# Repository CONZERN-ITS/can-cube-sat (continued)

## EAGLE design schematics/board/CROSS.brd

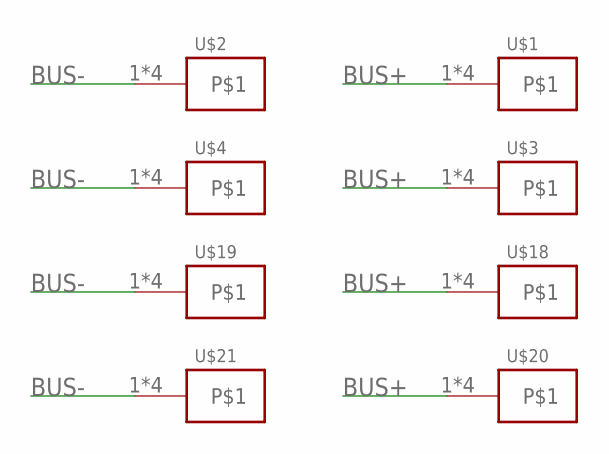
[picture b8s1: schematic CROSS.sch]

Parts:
U$1, U$2, U$3, U$4, U$18, U$19, U$20, U$21: KCONNECT-

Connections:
BUS+: U$1.1, U$1.2, U$1.3, U$1.4, U$3.1, U$3.2, U$3.3, U$3.4, U$18.1, U$18.2, U$18.3, U$18.4, U$20.1, U$20.2, U$20.3, U$20.4
BUS-: U$2.1, U$2.2, U$2.3, U$2.4, U$4.1, U$4.2, U$4.3, U$4.4, U$19.1, U$19.2, U$19.3, U$19.4, U$21.1, U$21.2, U$21.3, U$21.4

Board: 2 copper layers, 8 parts (0 on the bottom side), 2 nets, no tracks yet.

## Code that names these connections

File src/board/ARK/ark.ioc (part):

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Mcu.Name=STM32F103C(8-B)Tx
Mcu.Package=LQFP48
Mcu.UserName=STM32F103C8Tx
PA1.GPIOParameters=GPIO_Speed,PinState,GPIO_PuPd,GPIO_Label,GPIO_ModeDefaultOutputPP
PA1.GPIO_Label=BMS5
PA1.GPIO_ModeDefaultOutputPP=GPIO_MODE_OUTPUT_OD
PA1.GPIO_PuPd=GPIO_NOPULL
PA1.GPIO_Speed=GPIO_SPEED_FREQ_LOW
PA1.PinState=GPIO_PIN_SET
PA1.Signal=GPIO_Output
PA10.Mode=Asynchronous
PA10.Signal=USART1_RX
PA13.Mode=Serial_Wire
PA13.Signal=SYS_JTMS-SWDIO
PA14.Mode=Serial_Wire
PA14.Signal=SYS_JTCK-SWCLK
PA2.GPIOParameters=GPIO_Speed,PinState,GPIO_PuPd,GPIO_Label,GPIO_ModeDefaultOutputPP
PA2.GPIO_Label=BMS6
PA2.GPIO_ModeDefaultOutputPP=GPIO_MODE_OUTPUT_OD
PA2.GPIO_PuPd=GPIO_NOPULL
PA2.GPIO_Speed=GPIO_SPEED_FREQ_LOW
PA2.PinState=GPIO_PIN_SET
PA2.Signal=GPIO_Output
PA3.GPIOParameters=GPIO_Speed,PinState,GPIO_PuPd,GPIO_Label,GPIO_ModeDefaultOutputPP
PA3.GPIO_Label=BMS3
PA3.GPIO_ModeDefaultOutputPP=GPIO_MODE_OUTPUT_OD
PA3.GPIO_PuPd=GPIO_NOPULL
PA3.GPIO_Speed=GPIO_SPEED_FREQ_LOW
PA3.PinState=GPIO_PIN_SET
PA3.Signal=GPIO_Output
PA4.GPIOParameters=GPIO_Speed,PinState,GPIO_PuPd,GPIO_Label,GPIO_ModeDefaultOutputPP
PA4.GPIO_Label=BMS4
PA4.GPIO_ModeDefaultOutputPP=GPIO_MODE_OUTPUT_OD
PA4.GPIO_PuPd=GPIO_NOPULL
PA4.GPIO_Speed=GPIO_SPEED_FREQ_LOW
PA4.PinState=GPIO_PIN_SET
PA4.Signal=GPIO_Output
PA5.GPIOParameters=GPIO_Speed,PinState,GPIO_PuPd,GPIO_Label,GPIO_ModeDefaultOutputPP
PA5.GPIO_Label=BMS1
PA5.GPIO_ModeDefaultOutputPP=GPIO_MODE_OUTPUT_OD
PA5.GPIO_PuPd=GPIO_NOPULL
PA5.GPIO_Speed=GPIO_SPEED_FREQ_LOW
PA5.PinState=GPIO_PIN_SET
PA5.Signal=GPIO_Output
PA6.GPIOParameters=GPIO_Speed,PinState,GPIO_PuPd,GPIO_Label,GPIO_ModeDefaultOutputPP
PA6.GPIO_Label=BMS2
PA6.GPIO_ModeDefaultOutputPP=GPIO_MODE_OUTPUT_OD
PA6.GPIO_PuPd=GPIO_NOPULL
PA6.GPIO_Speed=GPIO_SPEED_FREQ_LOW
PA6.PinState=GPIO_PIN_SET
PA6.Signal=GPIO_Output
PA7.GPIOParameters=GPIO_Speed,PinState,GPIO_PuPd,GPIO_Label,GPIO_ModeDefaultOutputPP
PA7.GPIO_Label=OW
PA7.GPIO_ModeDefaultOutputPP=GPIO_MODE_OUTPUT_OD
PA7.GPIO_PuPd=GPIO_PULLUP
PA7.GPIO_Speed=GPIO_SPEED_FREQ_HIGH
PA7.PinState=GPIO_PIN_SET
PA7.Signal=GPIO_Output
PA9.Mode=Asynchronous
PA9.Signal=USART1_TX
PB0.GPIOParameters=GPIO_PuPd,GPIO_Label
PB0.GPIO_Label=PGOOD1
PB0.GPIO_PuPd=GPIO_PULLUP
PB0.Signal=GPIO_Input
PB1.GPIOParameters=GPIO_PuPd,GPIO_Label
PB1.GPIO_Label=PGOOD2
PB1.GPIO_PuPd=GPIO_PULLUP
PB1.Signal=GPIO_Input
PB10.Mode=I2C
PB10.Signal=I2C2_SCL
PB11.Mode=I2C
PB11.Signal=I2C2_SDA
PB14.GPIOParameters=PinState,GPIO_PuPd,GPIO_Label,GPIO_ModeDefaultOutputPP
PB14.GPIO_Label=DPC_RST
PB14.GPIO_ModeDefaultOutputPP=GPIO_MODE_OUTPUT_OD
PB14.GPIO_PuPd=GPIO_PULLUP
PB14.PinState=GPIO_PIN_SET
PB14.Signal=GPIO_Output
PB15.GPIOParameters=PinState,GPIO_PuPd,GPIO_Label,GPIO_ModeDefaultOutputPP
PB15.GPIO_Label=DPD_RST
PB15.GPIO_ModeDefaultOutputPP=GPIO_MODE_OUTPUT_PP
PB15.GPIO_PuPd=GPIO_PULLUP
PB15.PinState=GPIO_PIN_SET
PB15.Signal=GPIO_Output
PB5.GPIOParameters=GPIO_Speed,PinState,GPIO_PuPd,GPIO_Label,GPIO_ModeDefaultOutputPP
PB5.GPIO_Label=LED
PB5.GPIO_ModeDefaultOutputPP=GPIO_MODE_OUTPUT_OD
PB5.GPIO_PuPd=GPIO_NOPULL
PB5.GPIO_Speed=GPIO_SPEED_FREQ_LOW
PB5.PinState=GPIO_PIN_SET
PB5.Signal=GPIO_Output
PB6.GPIOParameters=GPIO_PuPd,GPIO_Label,GPIO_ModeDefaultEXTI
PB6.GPIO_Label=TIME
PB6.GPIO_ModeDefaultEXTI=GPIO_MODE_IT_FALLING
PB6.GPIO_PuPd=GPIO_NOPULL
PB6.Signal=GPXTI6
PB7.GPIOParameters=GPIO_Speed,PinState,GPIO_PuPd,GPIO_Label,GPIO_ModeDefaultOutputPP
PB7.GPIO_Label=I2C_INT
PB7.GPIO_ModeDefaultOutputPP=GPIO_MODE_OUTPUT_OD
PB7.GPIO_PuPd=GPIO_PULLUP
PB7.GPIO_Speed=GPIO_SPEED_FREQ_HIGH
PB7.PinState=GPIO_PIN_SET
PB7.Signal=GPIO_Output
PB8.Mode=I2C
PB8.Signal=I2C1_SCL
PB9.Mode=I2C
PB9.Signal=I2C1_SDA
PC13-TAMPER-RTC.GPIOParameters=GPIO_Speed,PinState,GPIO_Label,GPIO_ModeDefaultOutputPP
PC13-TAMPER-RTC.GPIO_Label=LED
PC13-TAMPER-RTC.GPIO_ModeDefaultOutputPP=GPIO_MODE_OUTPUT_OD
PC13-TAMPER-RTC.GPIO_Speed=GPIO_SPEED_FREQ_LOW
PC13-TAMPER-RTC.PinState=GPIO_PIN_SET
PC13-TAMPER-RTC.Signal=GPIO_Output
RCC.SYSCLKFreq_VALUE=64000000
RCC.SYSCLKSource=RCC_SYSCLKSOURCE_PLLCLK
board=custom

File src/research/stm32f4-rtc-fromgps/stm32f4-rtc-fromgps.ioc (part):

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Mcu.Name=STM32F407V(E-G)Tx
Mcu.Package=LQFP100
Mcu.UserName=STM32F407VETx
PA10.Mode=Asynchronous
PA10.Signal=USART1_RX
PA13.Mode=Serial_Wire
PA13.Signal=SYS_JTMS-SWDIO
PA14.Mode=Serial_Wire
PA14.Signal=SYS_JTCK-SWCLK
PA2.Mode=Asynchronous
PA2.Signal=USART2_TX
PA3.Mode=Asynchronous
PA3.Signal=USART2_RX
PA9.Mode=Asynchronous
PA9.Signal=USART1_TX
PC14-OSC32_IN.Mode=LSE-External-Oscillator
PC14-OSC32_IN.Signal=RCC_OSC32_IN
PC15-OSC32_OUT.Mode=LSE-External-Oscillator
PC15-OSC32_OUT.Signal=RCC_OSC32_OUT
PH0-OSC_IN.Mode=HSE-External-Oscillator
PH0-OSC_IN.Signal=RCC_OSC_IN
PH1-OSC_OUT.Mode=HSE-External-Oscillator
PH1-OSC_OUT.Signal=RCC_OSC_OUT
RCC.HSE_VALUE=8000000
RCC.SYSCLKFreq_VALUE=168000000
RCC.SYSCLKSource=RCC_SYSCLKSOURCE_PLLCLK
board=custom

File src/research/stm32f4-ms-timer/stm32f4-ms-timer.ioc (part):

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Mcu.Name=STM32F407V(E-G)Tx
Mcu.Package=LQFP100
Mcu.UserName=STM32F407VETx
PA0-WKUP.GPIOParameters=GPIO_Speed,GPIO_PuPd
PA0-WKUP.GPIO_PuPd=GPIO_PULLDOWN
PA0-WKUP.GPIO_Speed=GPIO_SPEED_FREQ_VERY_HIGH
PA0-WKUP.Signal=S_TIM2_CH1_ETR
PA10.Mode=Asynchronous
PA10.Signal=USART1_RX
PA6.GPIOParameters=GPIO_Speed,GPIO_PuPd
PA6.GPIO_PuPd=GPIO_PULLDOWN
PA6.GPIO_Speed=GPIO_SPEED_FREQ_VERY_HIGH
PA6.Signal=S_TIM3_CH1
PA7.GPIOParameters=GPIO_ModeDefaultPP,GPIO_Speed,GPIO_PuPd
PA7.GPIO_ModeDefaultPP=GPIO_MODE_AF_PP
PA7.GPIO_PuPd=GPIO_PULLDOWN
PA7.GPIO_Speed=GPIO_SPEED_FREQ_VERY_HIGH
PA7.Signal=S_TIM3_CH2
PA9.Mode=Asynchronous
PA9.Signal=USART1_TX
PC14-OSC32_IN.Mode=LSE-External-Oscillator
PC14-OSC32_IN.Signal=RCC_OSC32_IN
PC15-OSC32_OUT.Mode=LSE-External-Oscillator
PC15-OSC32_OUT.Signal=RCC_OSC32_OUT
PD12.GPIOParameters=GPIO_Speed,GPIO_PuPd
PD12.GPIO_PuPd=GPIO_PULLDOWN
PD12.GPIO_Speed=GPIO_SPEED_FREQ_VERY_HIGH
PD12.Signal=S_TIM4_CH1
PD13.GPIOParameters=GPIO_Speed,GPIO_PuPd
PD13.GPIO_PuPd=GPIO_PULLDOWN
PD13.GPIO_Speed=GPIO_SPEED_FREQ_VERY_HIGH
PD13.Signal=S_TIM4_CH2
PD2.GPIOParameters=GPIO_Speed
PD2.GPIO_Speed=GPIO_SPEED_FREQ_VERY_HIGH
PD2.Signal=S_TIM3_ETR
PE9.GPIOParameters=GPIO_Speed,GPIO_PuPd
PE9.GPIO_PuPd=GPIO_PULLDOWN
PE9.GPIO_Speed=GPIO_SPEED_FREQ_VERY_HIGH
PE9.Signal=S_TIM1_CH1
PH0-OSC_IN.Mode=HSE-External-Oscillator
PH0-OSC_IN.Signal=RCC_OSC_IN
PH1-OSC_OUT.Mode=HSE-External-Oscillator
PH1-OSC_OUT.Signal=RCC_OSC_OUT
RCC.HSE_VALUE=8000000
RCC.SYSCLKFreq_VALUE=168000000
RCC.SYSCLKSource=RCC_SYSCLKSOURCE_PLLCLK
board=custom

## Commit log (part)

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2020-04-27 Попытка исправить кнопку сброса времени
2020-04-28 Добавлена поддержка RGBA для графиков + настройки к предыдущему коммиту
2020-04-28 Добавлена функция удаления первых N точек ломаной + добавлна возможность отображения последних N точек
2020-04-29 GKS: поправлены поддержки
2020-04-30 GKS: поправлены привязки
2020-05-02 Закончен новый виджет + Переделаны цвета
2020-05-06 Изменения для поддержки Windows
2020-05-06 Код на момент совместного тестирования
2020-05-06 Одобренные партией правки энумераторов программных компонентов
2020-05-07 Небольшие изменения
2020-05-13 Добавление стандартной привязки ко времени
2020-05-13 Добавление математической модели
2020-05-13 Исправлена ошибка при разборе пакета NAV_SOL. Обновлен пакет NAV_SOL
2020-05-17 Удалил старые файлы. Они переехали в ./drivers
2020-05-17 Первые наброски для софта платы полезной нагрузки
2020-05-19 GKS: Вдогонку
2020-05-20 Маленький фикс проверки валидности напряжений
2020-05-20 Утилиты для генерации конфигурации u-blox
2020-05-21 Продолжение работ над оснасткой ЭМ ch_3
2020-05-23 Начата работа над улучшением модельки
2020-05-28 Доделаны сообщения модуля полезной нагрузки
2020-05-29 Оказывается единицы измерения в .xml файле мавлинка идут в код. Поэтому ненадо там писать всякие изыски
2020-05-30 Добавила установку в CMakeLists.txt
2020-05-31 Внутренний термистор теперь тоже можно опрашивать
2020-06-01 GKS: Исправлена модель по результатам печати
2020-06-01 Максимум упрощения для mics6814. Все это было лишнее имхо
2020-06-02 me2o2... отлажен?
2020-06-05 Все датчики более менее работают и даже немного калибруются
2020-06-14 Багфикс. Счетчик таймера TIM4 никогда не будет больше 0xFFFF0000, потому что он 16-тибитный
2020-06-14 Разработка полезной нагрузки идет во всю силу
2020-06-14 В плате полезной нагрузки включен IWDG
2020-06-24 Исправлена проблема с SNTP сервером
    Раньше адрес NTP-сервера получался по DHCP. Мы его отключили, так
    как на борту он не особо нужен будет. Поэтому ESP32 не мог
    отправлять запросы на синхронизацию.
    Понемногу пытаюсь писать комменатарии к коду. Теперь я полностью
    определился, что буду писать их на русском, поэтому они
    понемногу будут появляться.
2020-06-25 Синхронизация времени между ESP32
    Добавлен NTP сервер. Он будет работать в кубе с stmf4, который
    будет получать время от gps. Так что это получается stratum 1.
    Вот только из-за выполнения нескольких задач, время отправления
    может быть неточным.
2020-06-25 Ассерты и ErrorHandler Хала теперь перезапускают систему Настроена периодичность пакетов
2020-07-01 Изменение в виджете данных + убран текстовый лог + изменения в data_control
2020-07-01 Исправлено опускание i2c-int и разные фиксы
    I2C-INT неправильно работал. Теперь он опускается и поднимается
    своевременно.
    Пытаемя застваить работать ПН. Пока не очень.
2020-07-02 GKS: поправлены размеры кронштейна и отверстие в защитном кожухе
2020-07-03 Исправление для настроек + незначительное исправление
2020-07-10 SP, убраны диоды, изменены площадки, добавлены надписи
2020-07-11 Добавил в .gitignore файлы с расширением STL
2020-07-14 подготовка к тесту dm422
2020-07-14 Исправлены недочеты
2020-07-15 Точно рабочий код АРКа, ПН, БКУ
    Забыл добавить файлы к позапрошлому коммиту. Это очень грустно!
2020-07-16 Заменены ID компонент и систем для АРКа
    Раньше было 42. Теперь нормальное число.
2020-07-16 БСК теперь ищет БКУ через Wi-Fi после отключения
2020-07-16 Глобальная переработка + доработка для введения рассылки
2020-07-17 Доделана программа для приема радиопакетов на земле
2020-07-18 Принятие первой порции фиксов
2020-07-18 Добавлен драйвер встроенного термодатчика
    Стмовский АЦП сложен в управлении. Но на АЦП висит лишь термодатчик, а
    значит все намного проще, чем обычно.
    Забыл закинуть в предыдущий коммит
    Это тоже
2020-07-18 Изменены настройки на более нормальные
2020-07-18 Синронизация времени между СИНС и БКУ работает
    Теперь все работает.
2020-07-18 Перенос кода в отдельную папку
2020-07-21 Добавлен пакет для RSSI
2020-07-22 Исправлена отправка пакету дальше
2020-07-23 Исправление драйвера и подготовка к тесту
2020-07-24 Изменен АРК
2020-07-25 Улучшен ADC на АРКе
    Теперь встроен оверсэмплинг! И добавлен вывод на шину телеметрии.
2020-07-28 SC: Корректировка моделей по результатам печати
2020-07-28 В КА измененя в размерах кронштейна
2020-07-28 В догонку
2020-07-29 Парсер работает. Добавлена отправка правильных system_id и component_id для rssi пакетов
2020-07-30 Радио теперь разделяет сообщения по отправителю
    Раньше сообщения разелялись только по msgid. Однако из-за этого
    сообщения одного типа от разных источников могли заглушаться одним
    из источников. Теперь добавилось разделение с помощью динамического
    добавления контейнеров.
2020-07-30 Добавлено определение основы получения времени
2020-07-30 Цвета не работают
2020-07-30 Исправлен формат даты и времени для выходной директории
2020-08-01 Продолжение
2020-08-05 Добавила третий столбец в таблицу + настройка
2020-08-07 Добавлены выключатели для пакетов таблицы + настройки через переменную окружения
2020-08-12 Подготовлены к производству платы ARK v1.1 и SP v 1.2
2020-08-12 Добавлены модуль SD и удаление очереди в route
    Рабочий модуль для работы с SD картой. Известна проблема, что при
    отключения SD карты и обратной вставки эта карта больше не использется
    микроконтролером.
    Теперь можно удалять свою очередь из route после того, как она
    становится ненужной.
2020-08-12 Добавлены шаблоны настроек + изменены дефолтные настройки
2020-08-12 Добавлен README, содержащий в том числе инструкцию по настройке приложения
2020-08-15 начало отладки датчиков
2020-08-15 На БСК1 или на БКУ пины I2C_INT и LED перепутаны
    Проблема решена успешно
2020-08-15 Уменьшение логов и добавление подтяжки
    Забыли вставить подтяжку на плату >_<
2020-08-15 Определены состояния платы по джамперу. Начата проработка сосотояний
2020-08-15 Добавил проект для маяка для теста дальнобойности радио
2020-08-21 GKS: Модернизация наземки в части увеличения АБ до 4-х штук
2020-08-26 Убрана возможность пересылать полученные сообщения
2020-08-27 Исправление ошибок
2020-08-29 GKS: сделано отверстие под разъем питания
2020-08-29 Еще исправления
2020-08-29 Обработка ошибки повторяющихся данных
2020-09-01 GKS: создан com_port
2020-09-02 Увеличена надежность SD
2020-09-02 Доделан вочдог
2020-09-02 Добавлен файл, который удерживает папку Inc ntp-сервера, без которой проект не собирается
2020-09-04 Опция для генерации списка команд проектом БКУ для проверки через CPPCHECK. И снова правка сабмодуля. Наконец-то я собрал проект...
2020-09-05 Не ждем конфигурации gps по началу
2020-09-06 Включили CSS. Пересели на HSI. Проверка кватерниона на нан
2020-09-06 Исправлена релизная конфигурация АРК
2020-09-06 Исправления конфигуаций PAYLOAD аналогичные исправлениям ARK
2020-09-06 PAYLOAD перевед на HSI с понижением частоты с 72Мгц до 64Мгц. Из-за этого перенстроен таймер службы времени
2020-09-08 Управляющие таски делают своб работу еще лучше
    Нагреватели теперь ограничиваются силой тока.
    Добавлена возможность управления питанием Payload.
    Параметры сдвиговых регистров теперь правильно ограничены.
2020-09-08 Изменены пины АРКа для соответствия с платами
2020-09-08 Ремонт файла проекта и .settings в гитигнор
2020-09-08 Добавил неблокирующую индикацию ребута для АРК
2020-09-08 Добавлен счетчик резетов и счетчик переконфигураций жпс
2020-09-09 Испревление в преобразовании типов
2020-09-09 Добавление задержки после передачи настроек магнитометра
2020-09-09 Добавление пересчета углов в градусы + исправление математики
2020-09-11 Исправление в примере для SINS
2020-09-11 Теперь собирается и для дебага
2020-09-12 Убрал пулдаун с TIME пина PAYLOAD
2020-09-12 ДОбавлена обработка ошибок. Сигналы SIGINT, SIGHUP, SIGTERM приводят к завершению работы программы. Вроде даже работает
2020-09-13 SC: Добавлены платы с DC-DC, внесены изменения в печатные детали для БКУ и СБ по результатам 3D печати, прочие правки...
2020-09-13 Правильные калибровочные коэффициенты для mics6814 для полетной платы
2020-09-13 Упрощенная версия АРКа для полурабочей платы
2020-09-13 Починены пины SPI и отключение SD
2020-09-13 Сохранение данных сдигового регистра в TP50
2020-09-14 Теперь компилится
2020-09-17 Убраны статики из заголовка в mavlink_comp
2020-09-19 Добавлены сообщения для антенной системы
2020-09-19 Добавлен интерфейс системы ручного управления антенной
2020-09-20 Пересмотренная конфигурация neo6. Дает PPS всегда
2020-09-20 SC: Модернизирована крышка антенны GPS, добавлены шайбы под антенну РМ, переделан адаптер корпусных модулей
2020-09-23 актуальный конфиг?
2020-09-23 Починили радио
2020-09-24 Пересмотрен подход к отключению шаговиков, добавлен нижний предел для углов поворота антенны, добавлен функционал для ручного управления, исправлены ошибки
2020-09-24 Исправлены ошибки в GPS, таймаут GPS выведен в конфиг
2020-09-26 Переосмысление виджета данных с добавлением подсчета пакетов
2020-09-27 Исправление комментариев + новые сообщения для наземки
2020-09-27 Добавлены функции для калиборовки магнитометра и акселерометра. Для их правильной работы необходимо включить соответствующие макросы в state.h и включить макрос CALIBRATION.
2020-09-27 Исправление ошибок + смена принципа работы функции установки нулевого уровня
2020-09-28 Канал WIFI, исправлен баг с iwdt
2020-09-28 Адреса 1w сенсоров захардкожены в esp32
2020-09-28 Всопомгательные скрипты для обработки mavlog файлов и gitignore на обработанные данные
2020-09-30 Исправлено поведение при наложении графиков
2020-09-30 Добавлены недостающие характеристики графиков
2020-10-01 Дефайны теперь правильные: у нас всего 6 1W устройств
2020-10-01 Радио отправляет только пакеты целиком, чтобы не сыпать отдельными байтиками
2020-10-01 Таск управления батарейками отключен Убраны таск опроса ины на втором
2020-10-01 Перезапуск esp, если вайфай не включился
2020-10-01 Подправила настройки
2020-10-01 Добавлена пересылка rssi
2020-10-02 грегорианские таймштампы в csv файлах и таймштампы получения пакетов из мавлинк лога
2020-10-05 Добавлен пересчет геоцентриеских ecef координат в lat-lon для пакетов ubx-nax-sol
2020-10-06 Полётная телеметрия
2020-10-10 Исправлен баг вылета первого и второго есп32
2020-10-10 Новый приоритет сообщений и убран коэфициент
2021-01-07 Bump lxml from 4.5.2 to 4.6.2 in /src/ground/rpi/radio_receiver
    Bumps [lxml](https://github.com/lxml/lxml) from 4.5.2 to 4.6.2.
    - [Release notes](https://github.com/lxml/lxml/releases)
    - [Changelog](https://github.com/lxml/lxml/blob/master/CHANGES.txt)
    - [Commits](https://github.com/lxml/lxml/compare/lxml-4.5.2...lxml-4.6.2)
2021-03-31 Bump lxml from 4.5.2 to 4.6.3 in /src/ground/laptop/StrelA-MS
    Bumps [lxml](https://github.com/lxml/lxml) from 4.5.2 to 4.6.3.
    - [Release notes](https://github.com/lxml/lxml/releases)
    - [Changelog](https://github.com/lxml/lxml/blob/master/CHANGES.txt)
    - [Commits](https://github.com/lxml/lxml/compare/lxml-4.5.2...lxml-4.6.3)
2021-12-13 Bump lxml from 4.5.2 to 4.6.5 in /src/ground/laptop/StrelA-MS
    Bumps [lxml](https://github.com/lxml/lxml) from 4.5.2 to 4.6.5.
    - [Release notes](https://github.com/lxml/lxml/releases)
    - [Changelog](https://github.com/lxml/lxml/blob/master/CHANGES.txt)
    - [Commits](https://github.com/lxml/lxml/compare/lxml-4.5.2...lxml-4.6.5)
    ---
    updated-dependencies:
2022-07-06 Bump lxml from 4.5.2 to 4.9.1 in /src/ground/rpi/radio_receiver
    Bumps [lxml](https://github.com/lxml/lxml) from 4.5.2 to 4.9.1.
    - [Release notes](https://github.com/lxml/lxml/releases)
    - [Changelog](https://github.com/lxml/lxml/blob/master/CHANGES.txt)
    - [Commits](https://github.com/lxml/lxml/compare/lxml-4.5.2...lxml-4.9.1)
    ---
    updated-dependencies:
